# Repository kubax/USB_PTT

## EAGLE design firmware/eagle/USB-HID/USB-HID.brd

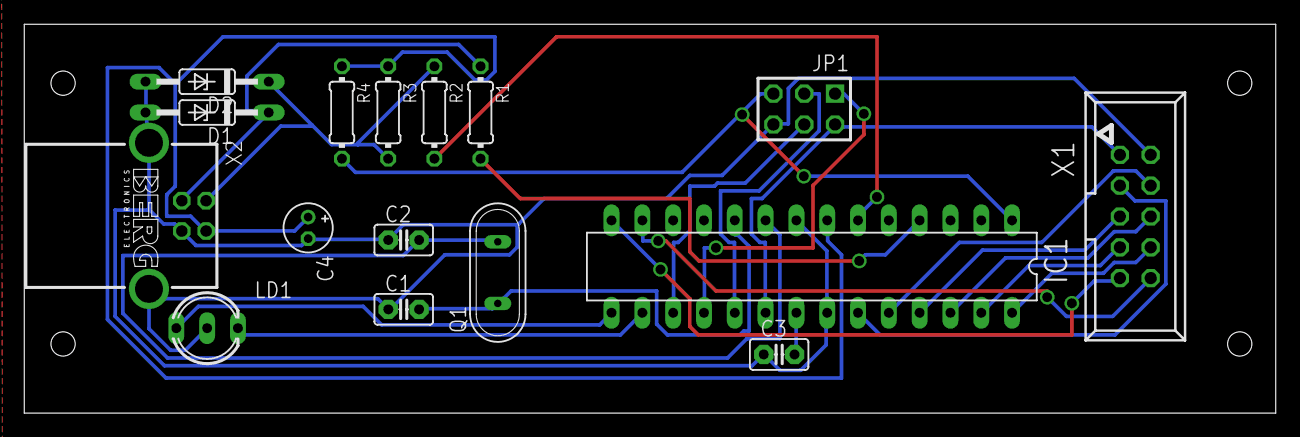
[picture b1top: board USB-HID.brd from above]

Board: 2 copper layers, 103.2 x 32.1 mm, 16 parts (0 on the bottom side), 24 nets.

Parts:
C1, C2: 27pF; C2.5-2
C3: 100nF; C2.5-2
C4: 4,7 microF; E1,8-4
D1, D2: 3,6V 0,5W; DO35Z10
IC1: MEGA8-P; DIL28-3
JP1: AVR-ISP-6VERT; AVR-ISP-6
LD1: DUOLED-A-5MM
Q1: 16 Mhz; QS
R1, R2: 68 Ohm; 0204/7
R3: 1,5k Ohm; 0204/7
R4: 10k Ohm; 0204/7
X1: 057-010-1
X2: PN61729-S

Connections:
GND: C1.1, C2.1, C3.1, C4.-, D1.A, D2.A, IC1.8, IC1.22, JP1.6, LD1.A, X1.2, X2.4, X2.S1, X2.S2
unnamed: C3.2, IC1.21
unnamed: C4.+, IC1.7, R3.1, R4.1, X2.1
unnamed: D2.C, R2.1, R3.2, X2.2
unnamed: D1.C, R1.1, X2.3
PB0: IC1.14, X1.9
PB1: IC1.15, LD1.CX
PB2: IC1.16, LD1.CR
PB3(MOSI): IC1.17, JP1.4
PB4(MISO): IC1.18, JP1.1
PB5(SCK): IC1.19, JP1.3
PB6(XTAL1): C2.2, IC1.9, Q1.2
PB7(XTAL2): C1.2, IC1.10, Q1.1
PC0: IC1.23, X1.3
PC1: IC1.24, X1.4
PC2: IC1.25, X1.5
PC3: IC1.26, X1.6
PC4: IC1.27, X1.7
PC5: IC1.28, X1.8
PC6(RESET): IC1.1, JP1.5, R4.2
PD7: IC1.13, X1.10
USB_D+: IC1.4, R1.2
USB_D-: IC1.6, R2.2
VCC: IC1.20, JP1.2, X1.1

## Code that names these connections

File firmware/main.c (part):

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#define BUTTON_PIN2 PIND

/* Define Button Bits */
#define BUTTON_BIT1 PC0
#define BUTTON_BIT2 PC1
#define BUTTON_BIT3 PC2
#define BUTTON_BIT4 PC3
#define BUTTON_BIT5 PC4
#define BUTTON_BIT6 PC5
#define BUTTON_BIT7 PB0
#define BUTTON_BIT8 PD7


#include <avr/io.h>
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
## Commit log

2012-05-22 Intial Commit
2012-05-22 Cleaned up Initial Commit
    Deleted repo within repo.
    Hoppefully fixed gitignore to ignore Release directory.
2012-05-22 Deleted Release Directory
    [x] and this time, i mean it!
2012-05-22 added Eagle shematics
    added Eagle shematics and Board Layout.
    Also added gitignore entries for eagle related files
2012-07-01 Bumped to API Version 17

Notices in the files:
firmware/main.c:
Copyright: (c) 2008 by OBJECTIVE DEVELOPMENT Software GmbH
License: GNU GPL v2 (see License.txt), GNU GPL v3 or proprietary (CommercialLicense.txt)
